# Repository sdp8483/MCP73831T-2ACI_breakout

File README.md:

Single cell lipo charger, 500mA

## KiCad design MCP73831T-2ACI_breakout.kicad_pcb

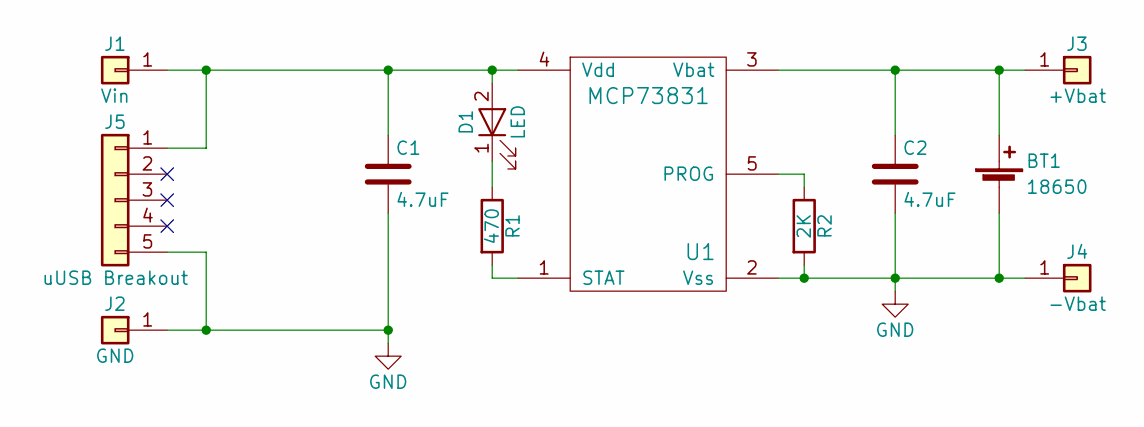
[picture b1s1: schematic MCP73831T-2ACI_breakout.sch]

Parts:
BT1: 18650; 18650_battery_holder_PCB_Pins; Mfg Part Number NONE
C1, C2: 4.7uF; C_1206_HandSoldering; Mfg Part Number NONE
D1: LED; LED_0805_HandSoldering
J1: Vin; SolderWirePad_single_SMD_5x10mm; Mfg Part Number NONE
J2: GND; SolderWirePad_single_SMD_5x10mm; Mfg Part Number NONE
J3: +Vbat; SolderWirePad_single_SMD_5x10mm; Mfg Part Number NONE
J4: -Vbat; SolderWirePad_single_SMD_5x10mm; Mfg Part Number NONE
J5: uUSB Breakout; Pin_Header_Straight_1x05_Pitch2.54mm; Mfg Part Number NONE
R1: 470; R_0805_HandSoldering; Mfg Part Number NONE
R2: 2K; R_0805_HandSoldering; Mfg Part Number NONE
U1: MCP73831; SOT-23-5_HandSoldering

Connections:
GND: BT1.2 (-), C1.2, C2.2, J2.1, J4.1, J5.5, R2.2, U1.2 (Vss)
unnamed: BT1.1 (+), C2.1, J3.1, U1.3 (Vbat)
unnamed: C1.1, D1.2 (A), J1.1, J5.1, U1.4 (Vdd)
unnamed: D1.1 (K), R1.1
unnamed: R1.2, U1.1 (STAT)
unnamed: R2.1, U1.5 (PROG)

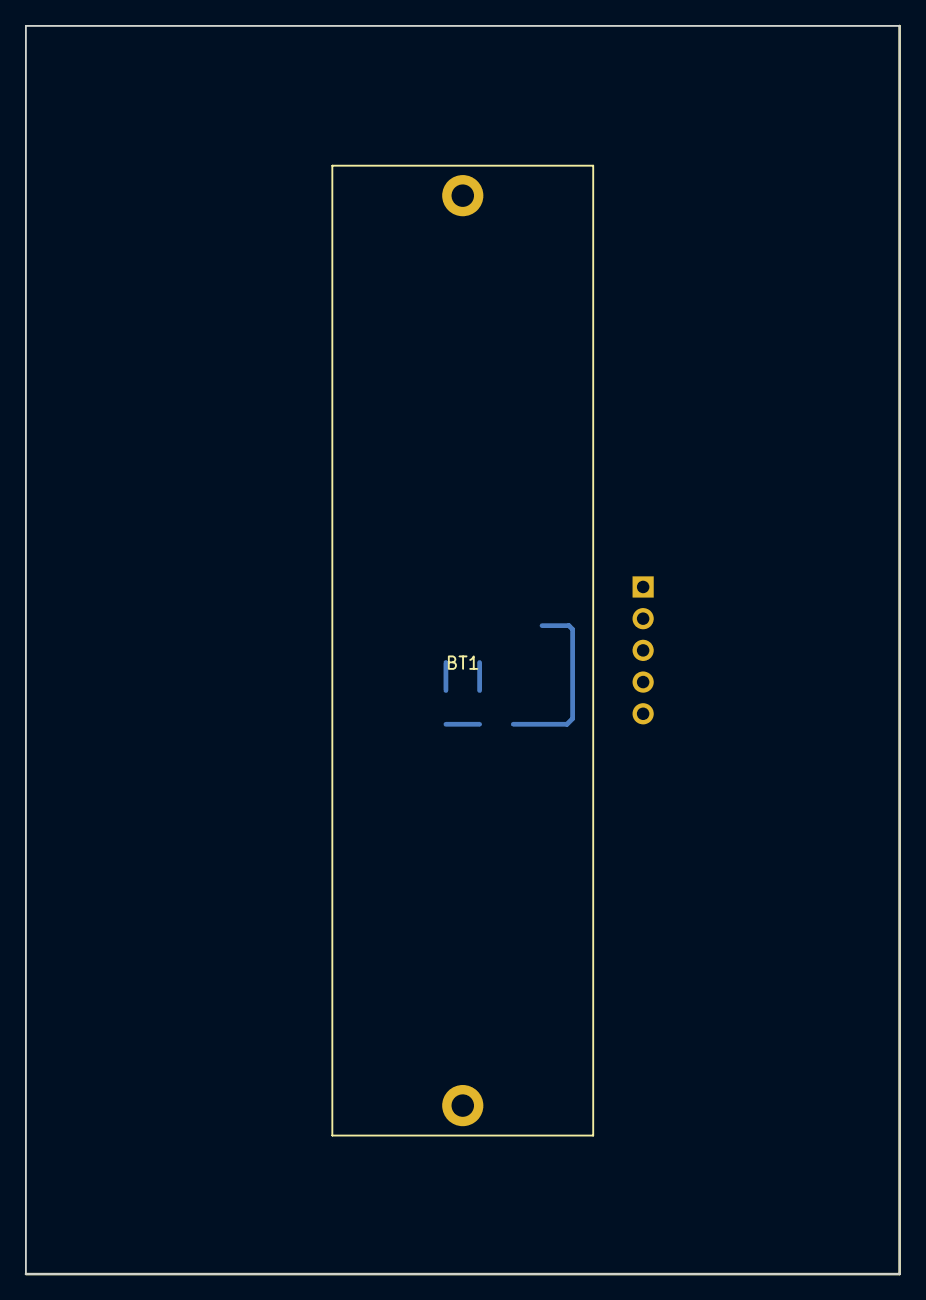
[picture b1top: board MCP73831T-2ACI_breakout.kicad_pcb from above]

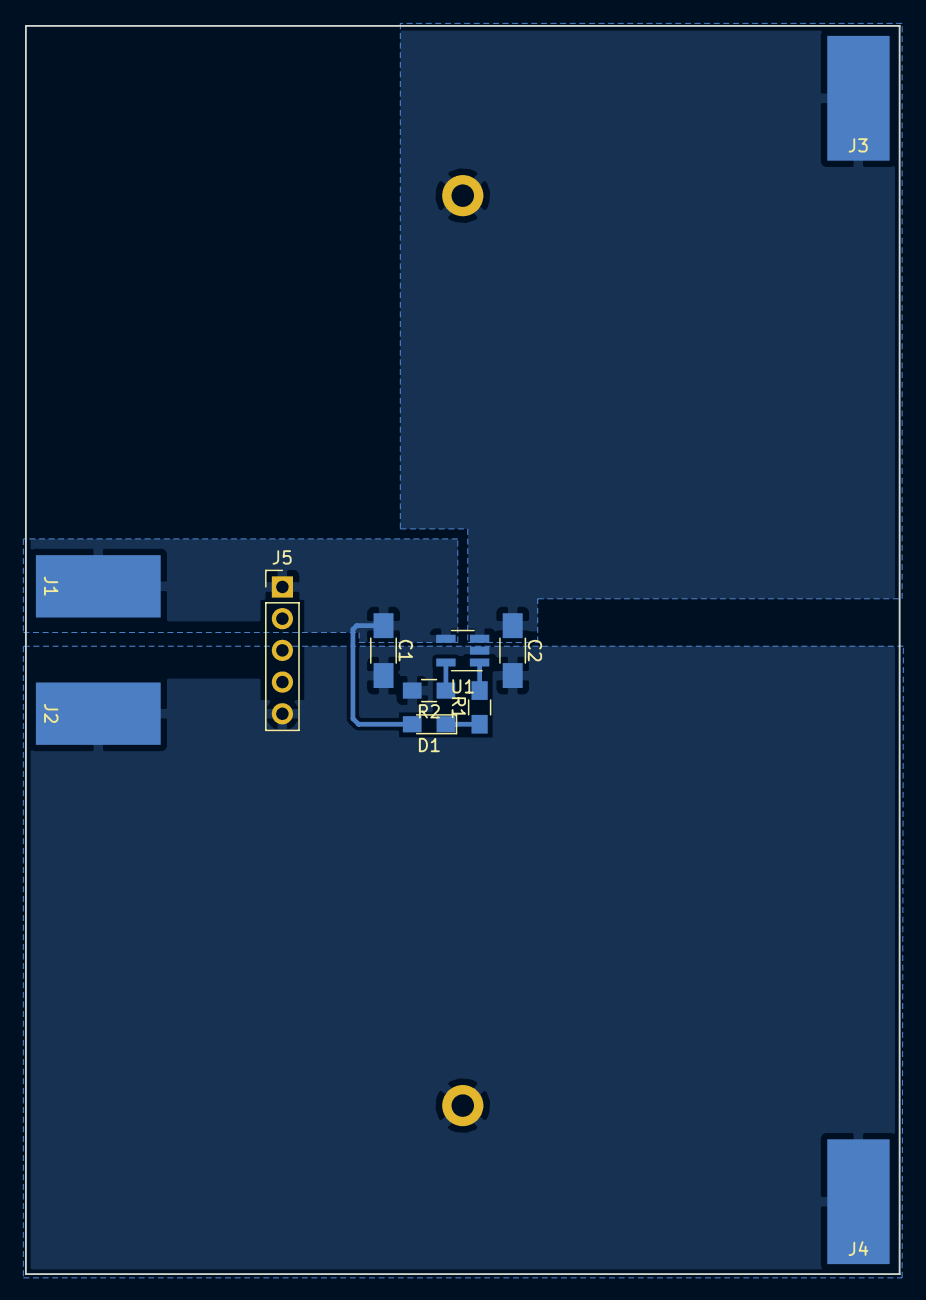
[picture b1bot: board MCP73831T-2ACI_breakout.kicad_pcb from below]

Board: 2 copper layers, 70.0 x 100.0 mm, 12 parts (11 on the bottom side), 6 nets.

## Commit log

2018-01-28 init commit
2018-01-28 updated to be project specific but vague
